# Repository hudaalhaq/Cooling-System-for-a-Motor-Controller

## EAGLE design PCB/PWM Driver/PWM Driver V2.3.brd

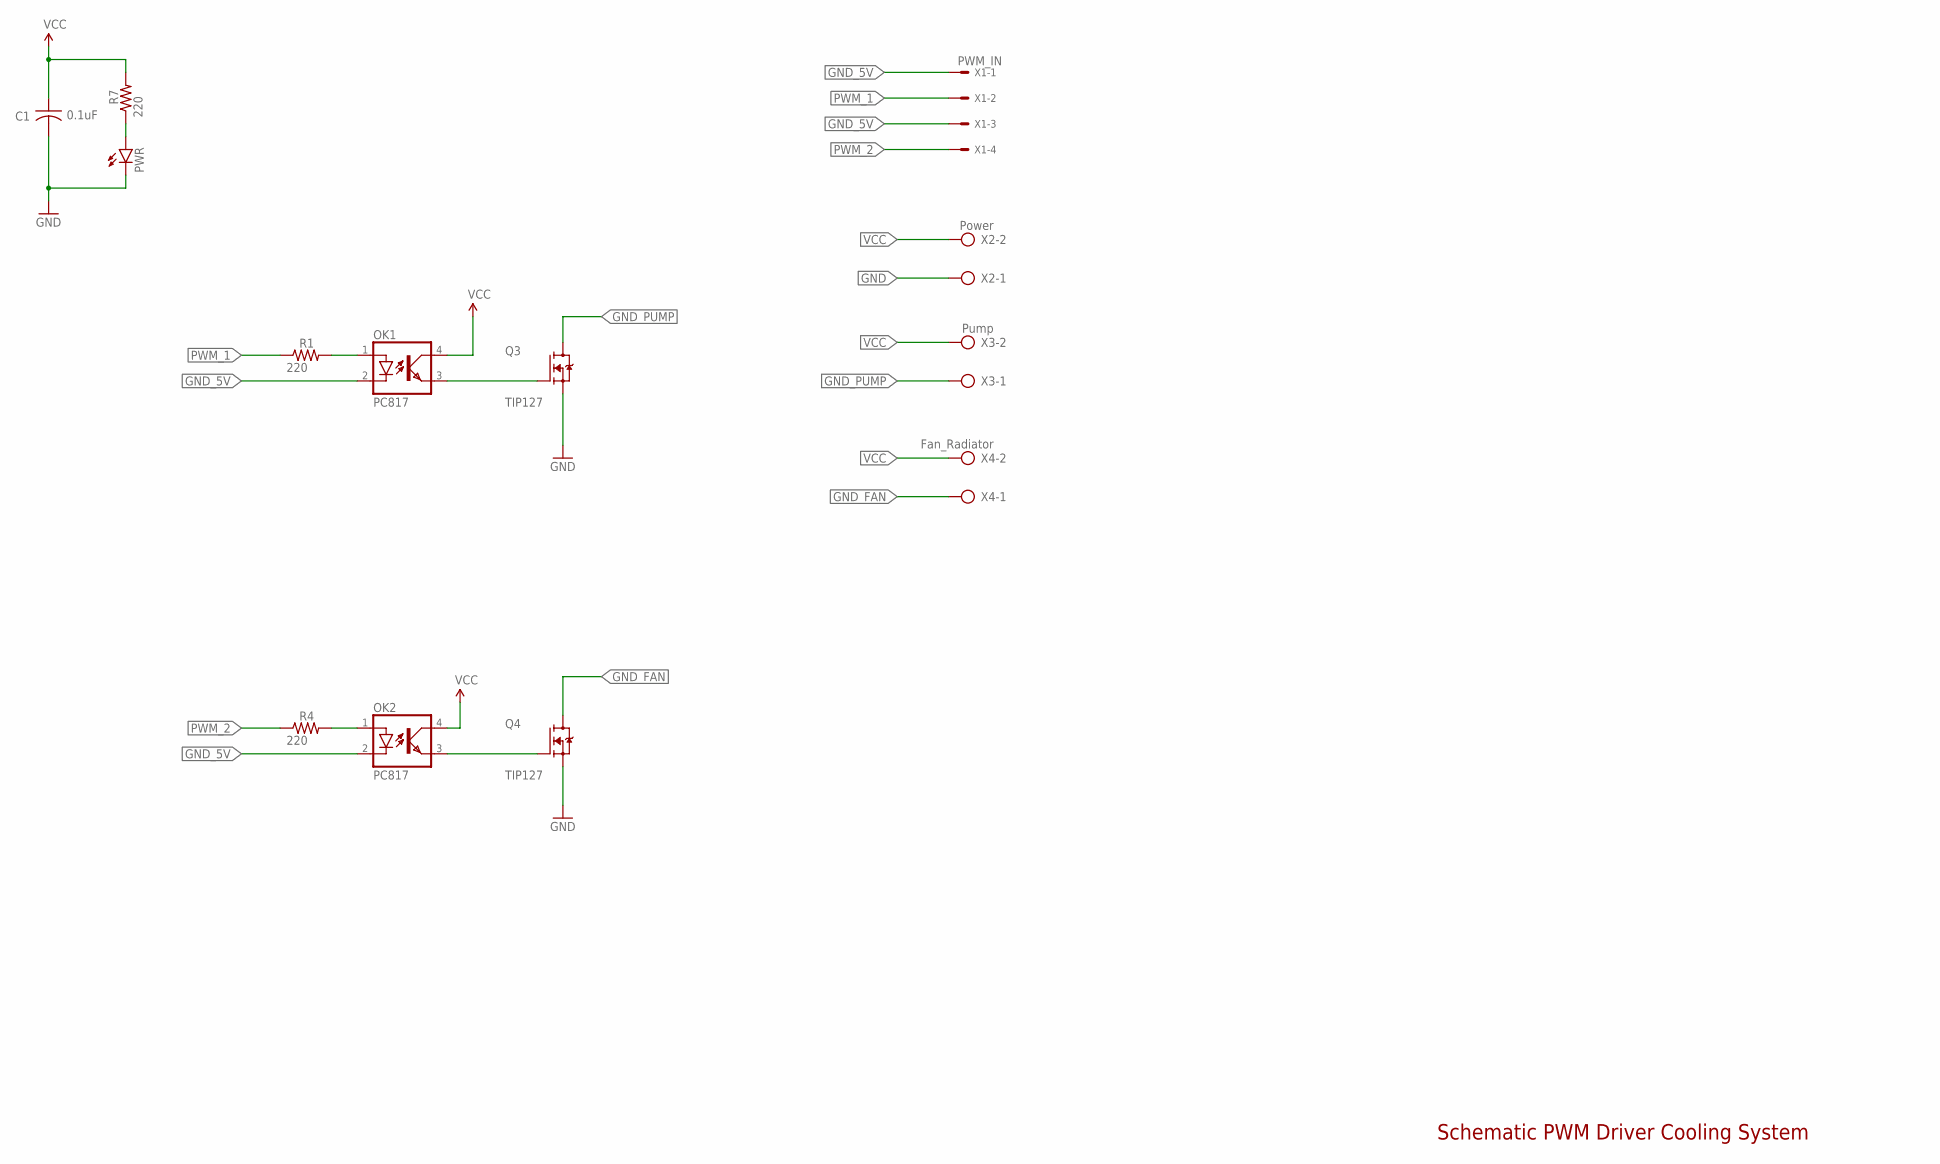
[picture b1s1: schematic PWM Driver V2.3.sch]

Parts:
C1: 0.1uF; C050-030X075
OK1, OK2: PC817; DIL04
PWR: LED5MM
Q3, Q4: TIP127; TO254P1041X444X2933-3
R1, R4, R7: 220; 0207/10
X1: PWM_IN; 22-23-2041
X2: Power; AK500/2
X3: Pump; AK500/2
X4: Fan_Radiator; AK500/2

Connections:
GND: C1.2, PWR.K (C), Q3.3 (S), Q4.3 (S), X2.1
GND_5V: OK1.2 (C), OK2.2 (C), X1.1, X1.3
GND_FAN: Q4.2 (D), X4.1
GND_PUMP: Q3.2 (D), X3.1
unnamed: OK2.1 (A), R4.2
unnamed: OK1.1 (A), R1.2
unnamed: OK2.3 (EMIT), Q4.1 (G)
unnamed: OK1.3 (EMIT), Q3.1 (G)
unnamed: PWR.A, R7.1
PWM_1: R1.1, X1.2
PWM_2: R4.1, X1.4
VCC: C1.1, OK1.4 (COL), OK2.4 (COL), R7.2, X2.2, X3.2, X4.2

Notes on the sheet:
Schematic PWM Driver Cooling System

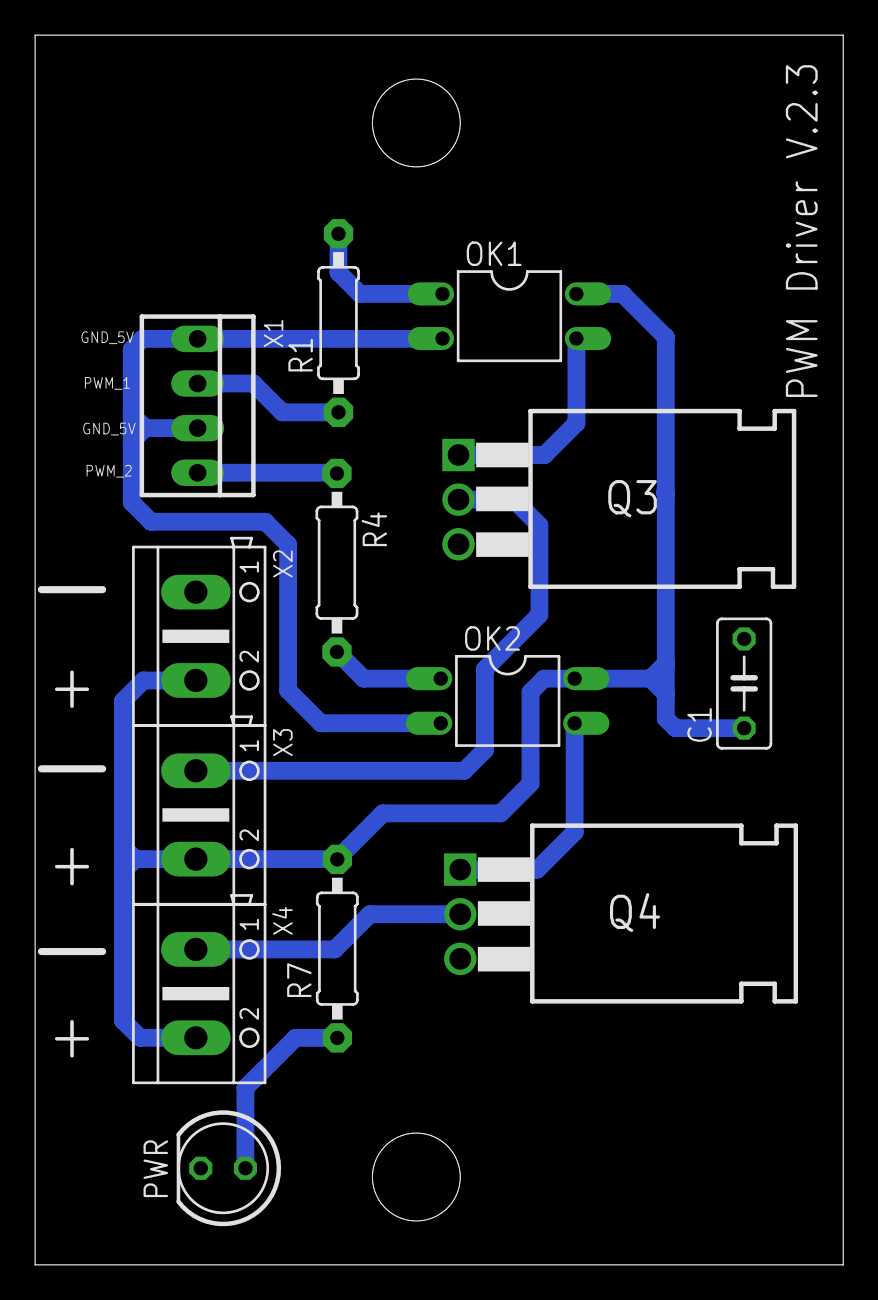
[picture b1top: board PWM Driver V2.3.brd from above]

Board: 2 copper layers, 46.0 x 70.0 mm, 13 parts (0 on the bottom side), 12 nets.

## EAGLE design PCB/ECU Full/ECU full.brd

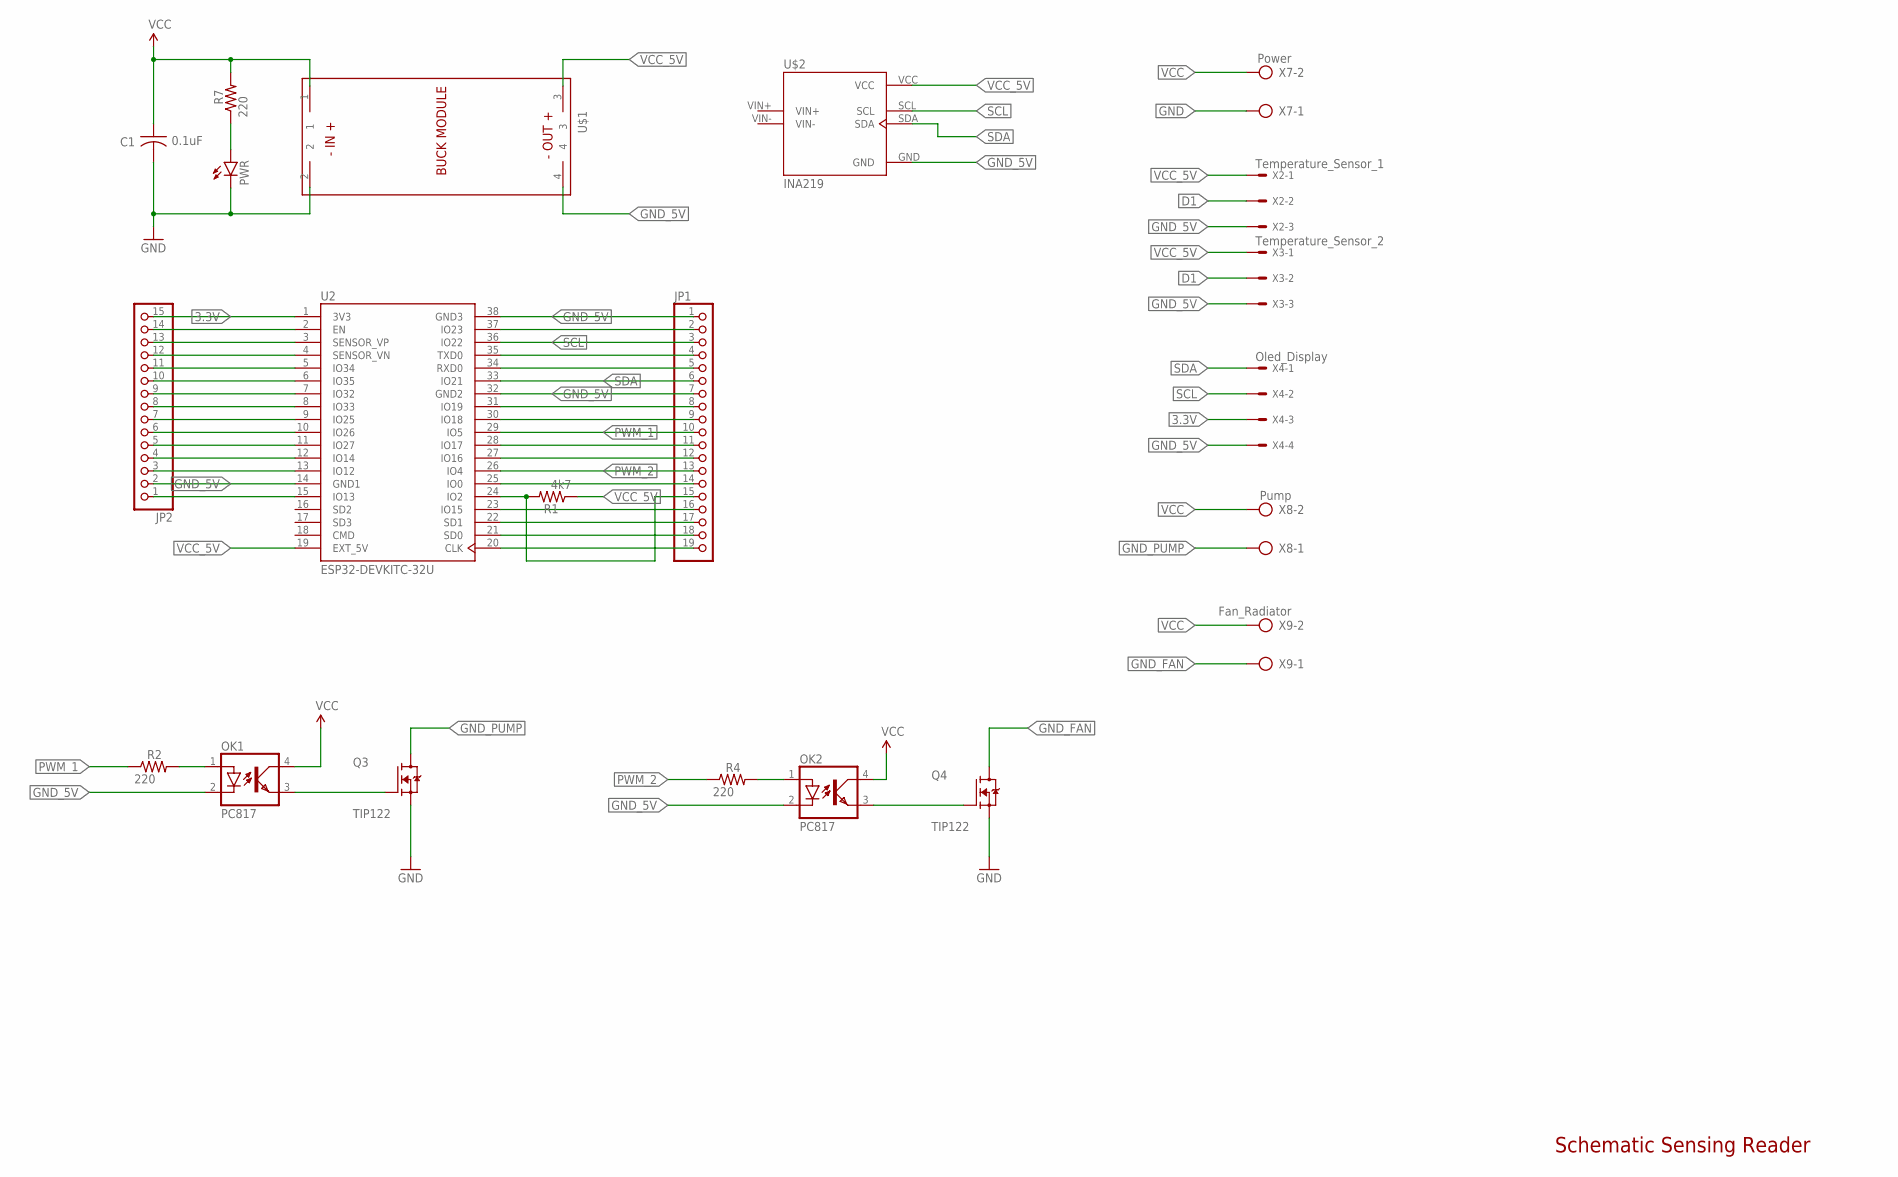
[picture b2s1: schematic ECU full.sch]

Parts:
C1: 0.1uF; C050-030X075
JP1: PINHD-1X19; 1X19
JP2: PINHD-1X15; 1X15
OK1, OK2: PC817; DIL04
PWR: LED5MM
Q3, Q4: TIP122; TO254P1041X444X2933-3
R1: 4k7; 0207/10
R2, R4, R7: 220; 0207/10
U2: ESP32-DEVKITC-32U; MODULE_ESP32-DEVKITC-32U
U$1: BUCK_MODULEWITH_SMDPADS&THROUGHHOLES; BUCK_MODULE
U$2: INA219
X2: Temperature_Sensor_1; 22-23-2031
X3: Temperature_Sensor_2; 22-23-2031
X4: Oled_Display; 22-23-2041
X7: Power; AK500/2
X8: Pump; AK500/2
X9: Fan_Radiator; AK500/2

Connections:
3.3V: JP2.15, U2.1 (3V3), X4.3
D1: JP1.15, R1.2, U2.24 (IO2), X2.2, X3.2
GND: C1.2, PWR.K (C), Q3.3 (S), Q4.3 (S), U$1.2, X7.1
GND_5V: JP1.1, JP1.7, JP2.2, OK1.2 (C), OK2.2 (C), U2.14 (GND1), U2.32 (GND2), U2.38 (GND3), U$1.4, U$2.GND, X2.3, X3.3, X4.4
GND_FAN: Q4.2 (D), X9.1
GND_PUMP: Q3.2 (D), X8.1
unnamed: OK1.1 (A), R2.2
unnamed: JP2.14, U2.2 (EN)
unnamed: JP2.13, U2.3 (SENSOR_VP)
unnamed: JP2.12, U2.4 (SENSOR_VN)
unnamed: JP2.11, U2.5 (IO34)
unnamed: JP2.10, U2.6 (IO35)
unnamed: JP2.9, U2.7 (IO32)
unnamed: JP2.8, U2.8 (IO33)
unnamed: JP2.7, U2.9 (IO25)
unnamed: JP2.6, U2.10 (IO26)
unnamed: JP2.5, U2.11 (IO27)
unnamed: JP2.4, U2.12 (IO14)
unnamed: JP2.3, U2.13 (IO12)
unnamed: JP2.1, U2.15 (IO13)
unnamed: OK1.3 (EMIT), Q3.1 (G)
unnamed: OK2.1 (A), R4.2
unnamed: OK2.3 (EMIT), Q4.1 (G)
unnamed: JP1.19, U2.20 (CLK)
unnamed: JP1.18, U2.21 (SD0)
unnamed: JP1.17, U2.22 (SD1)
unnamed: JP1.14, U2.25 (IO0)
unnamed: JP1.16, U2.23 (IO15)
unnamed: JP1.12, U2.27 (IO16)
unnamed: JP1.11, U2.28 (IO17)
unnamed: JP1.9, U2.30 (IO18)
unnamed: JP1.2, U2.37 (IO23)
unnamed: JP1.4, U2.35 (TXD0)
unnamed: JP1.5, U2.34 (RXD0)
unnamed: JP1.8, U2.31 (IO19)
unnamed: PWR.A, R7.1
PWM_1: JP1.10, R2.1, U2.29 (IO5)
PWM_2: JP1.13, R4.1, U2.26 (IO4)
SCL: JP1.3, U2.36 (IO22), U$2.SCL, X4.2
SDA: JP1.6, U2.33 (IO21), U$2.SDA, X4.1
VCC: C1.1, OK1.4 (COL), OK2.4 (COL), R7.2, U$1.1, X7.2, X8.2, X9.2
VCC_5V: R1.1, U2.19 (EXT_5V), U$1.3, U$2.VCC, X2.1, X3.1

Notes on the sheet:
Schematic Sensing Reader

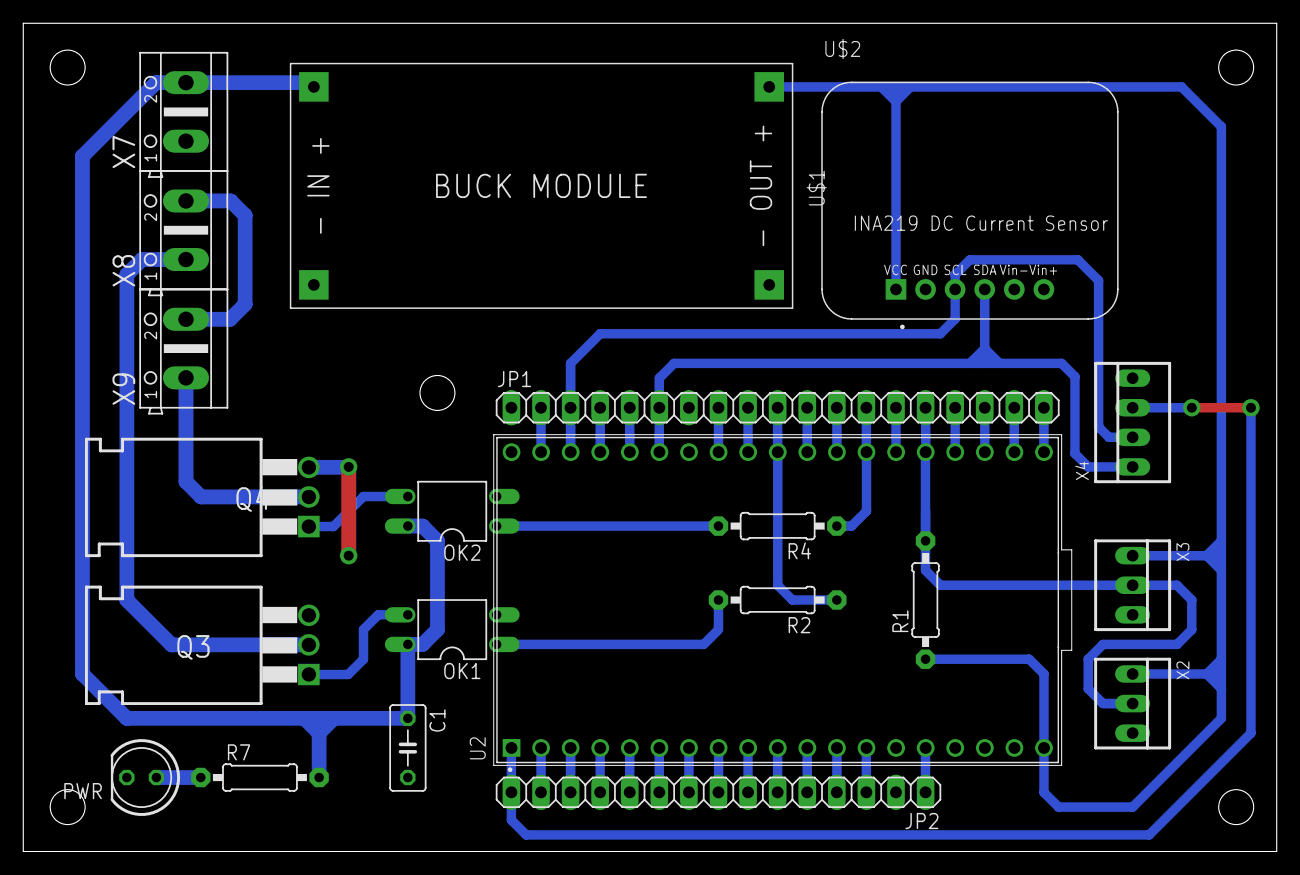
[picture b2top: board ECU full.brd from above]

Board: 2 copper layers, 107.6 x 71.1 mm, 21 parts (0 on the bottom side), 42 nets.

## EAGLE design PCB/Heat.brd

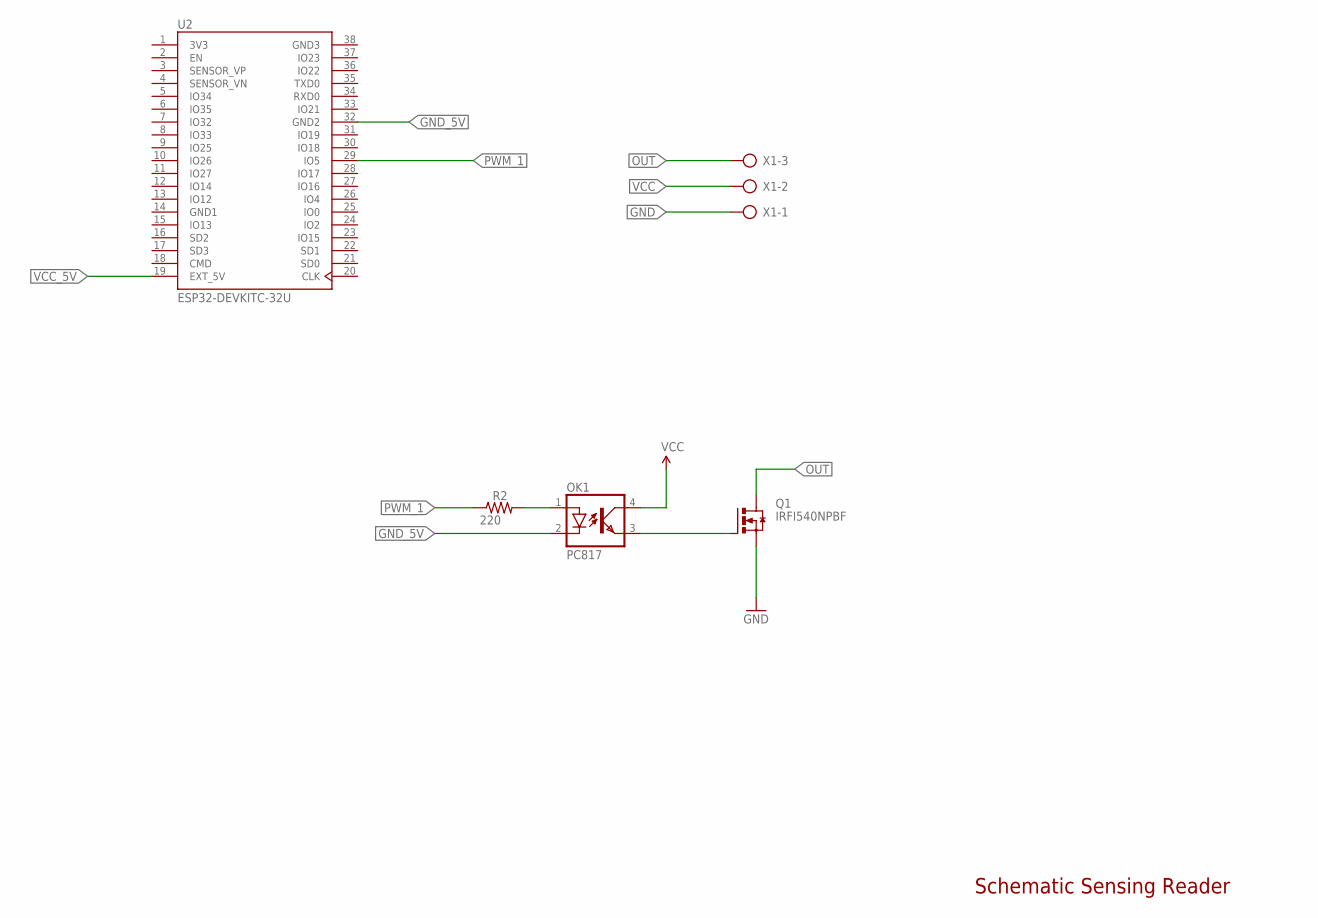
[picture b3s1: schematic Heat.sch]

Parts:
OK1: PC817; DIL04
Q1: IRFI540NPBF; TO220BH
R2: 220; 0207/10
U2: ESP32-DEVKITC-32U; MODULE_ESP32-DEVKITC-32U
X1: AK500/3-H

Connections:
3V3: U2.1 (3V3)
GND: Q1.S, X1.1
GND1: U2.14 (GND1)
GND3: U2.38 (GND3)
GND_5V: OK1.2 (C), U2.32 (GND2)
unnamed: OK1.1 (A), R2.2
unnamed: OK1.3 (EMIT), Q1.G
OUT: Q1.D, X1.3
PWM_1: R2.1, U2.29 (IO5)
VCC: OK1.4 (COL), X1.2
VCC_5V: U2.19 (EXT_5V)

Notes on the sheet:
Schematic Sensing Reader

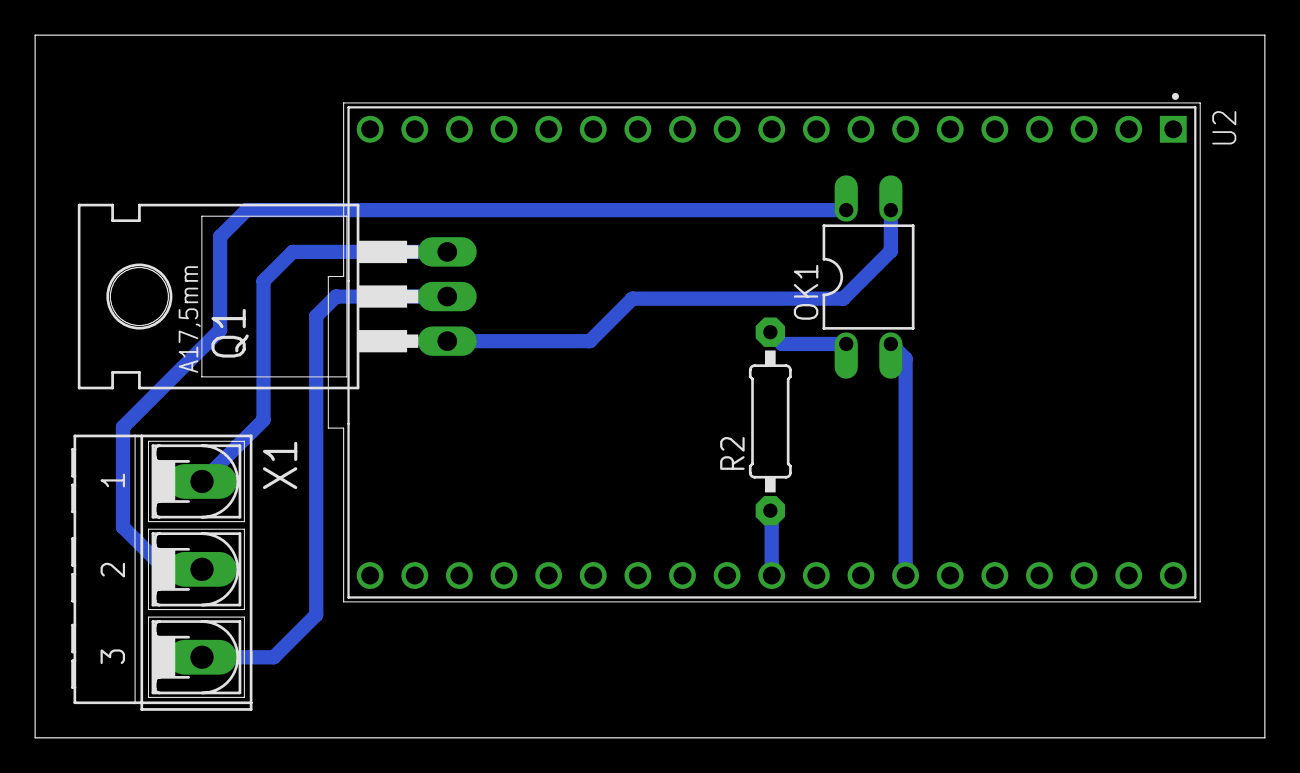
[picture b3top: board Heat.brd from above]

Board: 2 copper layers, 70.0 x 40.0 mm, 5 parts (0 on the bottom side), 7 nets.

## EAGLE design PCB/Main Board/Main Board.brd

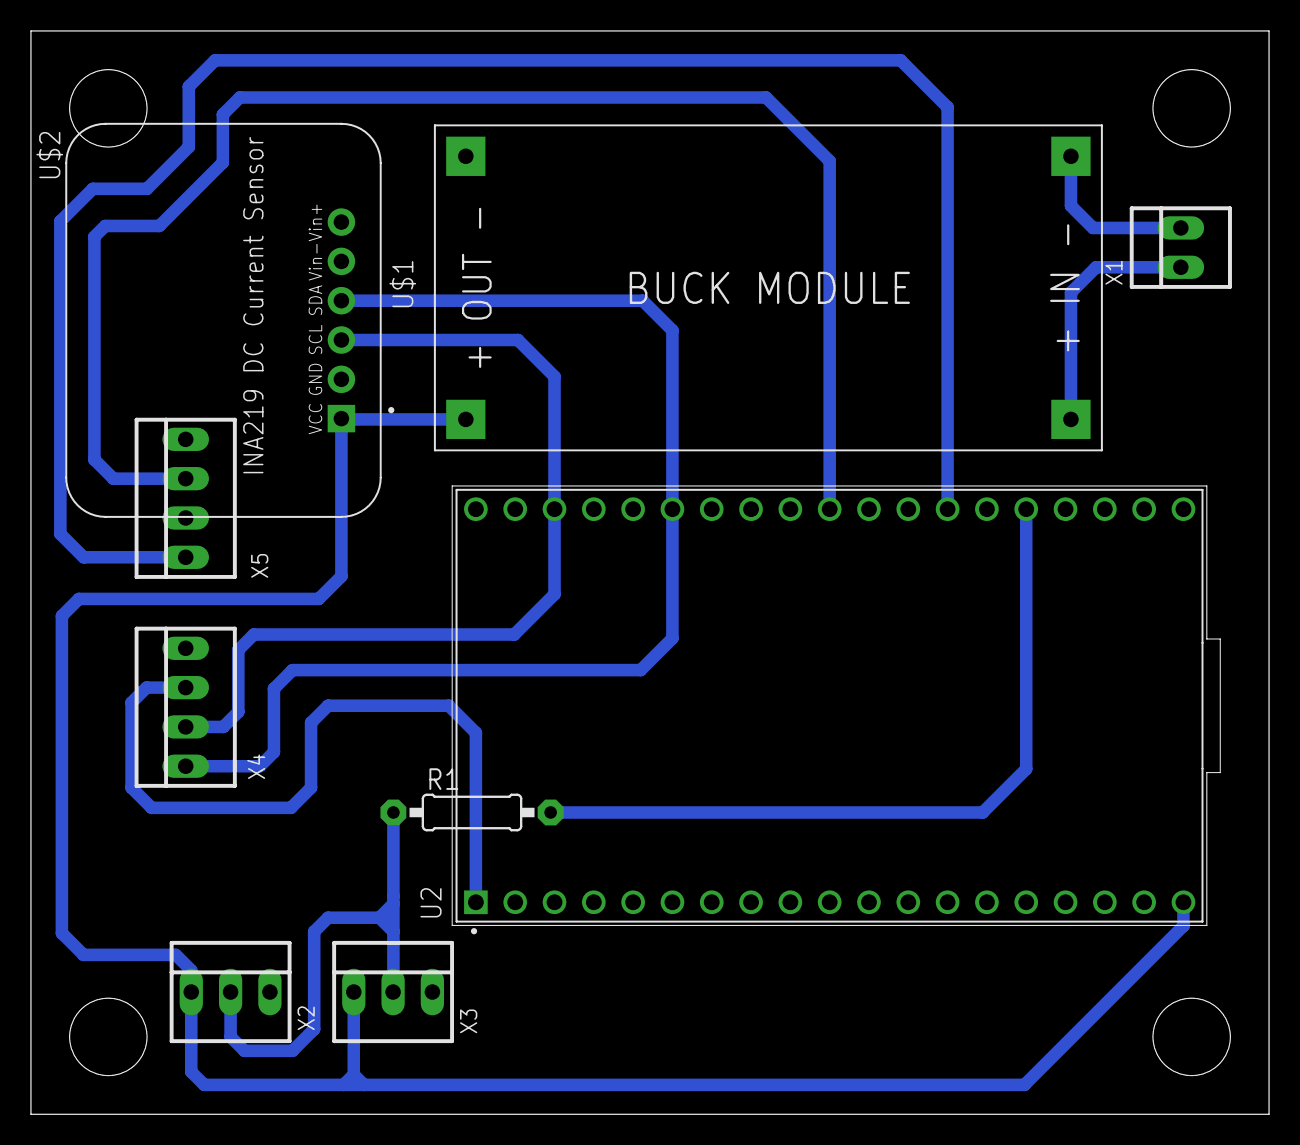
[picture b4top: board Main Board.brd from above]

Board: 2 copper layers, 80.0 x 70.0 mm, 9 parts (0 on the bottom side), 11 nets.

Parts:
R1: 4k7; 0207/10
U2: ESP32-DEVKITC-32U; MODULE_ESP32-DEVKITC-32U
U$1: BUCK_MODULEWITH_SMDPADS&THROUGHHOLES; BUCK_MODULE
U$2: INA219
X1: Power; 22-23-2021
X2: Temperature_Sensor_1; 22-23-2031
X3: Temperature_Sensor_2; 22-23-2031
X4: Oled_Display; 22-23-2041
X5: PWM_OUT; 22-23-2041

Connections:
3.3V: U2.1, X4.3
D1: R1.1, X2.2, X3.2
GND: U2.14, U2.32, U2.38, U$1.4, U$2.GND, X2.3, X3.3, X4.4, X5.2, X5.4
IN+: U$1.1, X1.1
IN-: U$1.2, X1.2
unnamed: R1.2, U2.24
PWM_1: U2.29, X5.3
PWM_2: U2.26, X5.1
SCL: U2.36, U$2.SCL, X4.2
SDA: U2.33, U$2.SDA, X4.1
VCC: U2.19, U$1.3, U$2.VCC, X2.1, X3.1

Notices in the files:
parts and their libraries:
SparkFun: Licensing: CC v3.0 Share-Alike You are welcome to use this library for commercial purposes.
